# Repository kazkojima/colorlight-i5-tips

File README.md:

# Colorlight i5 Tips

This is a tiny collection of tips for [Colorlight i5 FPGA board](https://github.com/wuxx/Colorlight-FPGA-Projects).

## Quick start

See [Tom Verbeure's great article](https://tomverbeure.github.io/2021/01/22/The-Colorlight-i5-as-FPGA-development-board.html) first. It's a complete guide for the board and its environment ATM.

See also [get-start](https://github.com/wuxx/Colorlight-FPGA-Projects/blob/master/get-start.md) of the above original site. The board has the CMSIS-DAP link for debug and serial port. The site gives the "dapprog" which is a wrapper script of OpenOCD for convenience.

```
$ ./dapprog xxx.svf # Configure with xxx.svf
$ ./dapprog xxx.bit # Write configuration to the flash
```

though the 2nd one fails because the flash is protected in shipping. See SPIFLASH below. If you follows the Tom's article, this problem can be avoided with "ecpdap".

```
$ ecpdap flash unprotect
```

See 'Programming a Bitstream into SPI flash' section of his article for details.
For loading and flash writing,

```
$ ecpdap program xxx.bit       # Configure with xxx.svf
$ ecpdap flash erase           # Erase flash
$ ecpdap flash write xxx.bit   # Write configuration to the flash
```

## LiteX

Now [litex-board](https://github.com/litex-hub/litex-boards) has colorlight i5 board support. It uses [Adam Greig's ecpdap](https://github.com/adamgreig/ecpdap) as the bit stream loader written in Rust.

For LiteX, see [Quick start guide of LiteX](https://github.com/enjoy-digital/litex#quick-start-guide).

```
$ wget https://raw.githubusercontent.com/enjoy-digital/litex/master/litex_setup.py
$ chmod +x litex_setup.py
$ ./litex_setup.py init install --user
```

should prepare the LiteX tree.

After these steps,

```
$ cd litex-boards/litex_boards/targets
$ ./colorlight_i5.py --with-sdcard --integrated-rom-size 0xc000 --l2-size 2048
```

for example, will generate .v and .lpf files in litex-boards/litex_boards/targets/build/colorlight_i5/gateware directory.

```
$ cd build/colorlight_i5/gateware
$ /bin/sh ./build_colorlight_i5.sh
```

will build .svf and .bin stream files.

With --build option

```
$ ./colorlight_i5.py --with-sdcard --with-spi --integrated-rom-size 0xc000 --l2-size 2048 --build
```

build_colorlight_i5.sh runs automatically. If ecpdap is installed already, --load option programs FPGA with the stream built

```
$ ./colorlight_i5.py --with-sdcard --with-spi --integrated-rom-size 0xc000 --l2-size 2048 --load
```

## SPIFLASH

[The start guide](https://github.com/wuxx/Colorlight-FPGA-Projects/blob/master/get-start.md) says that the SPI-Flash on i5 modules GD25Q16, is locked. You can free the lock with ecpdap.

## SDCARD

I've tested DIGILENT MicroSD PMOD.

It seems that the pull-up is a bit weak to work with the higher clock. An added 1k pull-up register to MOSI/CMD line works for me.

## Ethernet

Colorlight i5 has two Braodcom's B50612D gigabit ethernet transceiver chips. I made a simple extender with pulse transformer and RJ45 connector to test ethernet. i5ether directory includes KiCad files for it.

netboot works with it.

B50612D datasheet says that the pin 41 of the chip PHYA[0] determines the PHY Address of B50612D. It seems that the chip connected to ETH2_* connecter pins has PHYA[0] = 0 and the LiteX ether MAC works with this PHY. ~~ATM, the platform file defines this chip as the 2nd ether so as to match the connector pins.~~ The order of the two PHYs is swapped with the naming of the connectors on the board so to match with the configuration of their PHYA[0] pins. The default is "--eth-phy 0".

~~The build option "--eth-phy 1" will make ETH2_* pins the working ethernet port.~~

```
$ ./colorlight_i5.py --integrated-rom-size 0xc000 --l2-size 2048 --with-sdcard --with-ethernet
```

## HDMI

The build option "--with-video-framebuffer" (resp. "--with-video-terminal") makes the experimental support for video frame buffer (resp. video terminal) enable. The configuration of the HDMI output pins on the Muse-lab development board are assumed.

--with-video-framebuffer and --with-video-terminal will consume some RAM blocks of ECP5. If these options are used with --with-ethernet, for example, the build may fail due to the shortage of BRAM(DP16KD). One could reduce the usage of BRAM with specifying the lower values of integrated-sram-size and l2-size. Here are some examples.

```
$ ./colorlight_i5.py --with-ethernet --with-video-framebuffer --integrated-rom-size 0xa000 --integrated-sram-size 0x1000 --l2-size 2048 --build --load

$ ./colorlight_i5.py --with-ethernet --with-video-terminal --integrated-rom-size 0xa000 --integrated-sram-size 0x1000 --l2-size 1024 --build --load
```

The video fame buffer has a data skew issue on colorlight i5 ATM. It can be avoided temporarily with the one liner below:

```
diff --git a/litex_boards/targets/colorlight_i5.py b/litex_boards/targets/colorlight_i5.py
index 58aacfc..f081f43 100755
--- a/litex_boards/targets/colorlight_i5.py
+++ b/litex_boards/targets/colorlight_i5.py
@@ -150,7 +150,7 @@ class BaseSoC(SoCCore):
                 size                    = kwargs.get("max_sdram_size", 0x40000000),
                 l2_cache_size           = kwargs.get("l2_size", 8192),
                 l2_cache_min_data_width = kwargs.get("min_l2_data_width", 128),
-                l2_cache_reverse        = True
+                l2_cache_reverse        = False if with_video_framebuffer else True
             )
 
         # Ethernet / Etherbone ---------------------------------------------------------------------
```

## Zephyr

Links:

[Minimal Zephyr OS on RISC-V and other tests](https://blog.pcbxprt.com/index.php/2020/07/26/minimal-zephyr-os-on-risc-v-and-other-tests/)

[his github repo](https://github.com/ghent360/riscvOnColorlight-5A-75B)

Install Zephyr and make a modification for colorlight as written in the blog.

Although it may not be necessary in your environment, on my Ubuntu 20.04 TLS system, I needed a complete python-3.7 environment for building zephyr itself and its examples. It can be done

```
$ conda create --name py37 python=3.7
$ conda activate py37
```

if you have installed Anaconda.

Zephyr's Litex-vexrisc support expects 8-bit CSRs as well as linux. OTOH LiteX produces a 32-bit CSR SoC by default, so that needs to be changed with --csr-data-width 8 option.

```
$ ./colorlight_i5.py --with-sdcard --with-ethernet --integrated-rom-size 0xc000 --l2-size 2048 --csr-data-width 8
```

Also 2 DT-related zephyr's files

```
dts/riscv/riscv32-litex-vexriscv.dtsi
boards/riscv/litex_vexriscv/litex_vexriscv.dts
```

need to be modified for the changes in the configuration of the SoC, frequencies and the address of the CSRs. colorlight_i5.py generates build/colorlight_i5/software/include/generated/csr.h which contains the CSR's address information when building SoC RTL.

The simple example like blinky works successfully, though it looks some litex drivers in zephyr are WIP and not full-featured.

#### Updates for Zephyr

I've pushed [zephyr-rtos branch with modified DTS and default configs for colorlight-i5](https://github.com/kazkojima/zephyr/tree/colorlight_i5).

You can try net samples with it.

```
$ cd zephyrproject/zephyr/samples/net/telnet
$ mkdir build
$ cd build
$ cmake -DBOARD=litex_vexriscv ..
$ make menuconfig # optional
$ make
```

makes zephyr/zephyr.bin binary which can be used as a litex boot.bin.

## linux-on-litex-vexriscv

In the following sections, linux-on-litex-vexriscv HEAD and litex-hub/linux litex-rebase branch HEAD are assumed.

Due to the 8MB memory limit, it's difficult to put the root filesystem on the RAM like other boards. Putting it on NFS or micro SD will be a good candidate. Linux can boot on these two settings, though it's very slow. The main reason would be that there is not enough physical memory to keep a sufficient working set.

Since we have only 8GB of memory, we need to change the memory map for the device table and emulator binaries. The patch in linux/ assumes rv32.dtb at 0x40780000 and opensbi.bin at 0x407c0000.
There is a boot.json file in linux/ that matches this change.

### sdcard root

To make the micro SD the root FS, I'm using the litex-rebase branch of [litex's linux tree](https://github.com/litex-hub/linux.git), [a tiny patch for mmc](https://github.com/kazkojima/colorlight-i5-tips/blob/main/linux/linux-litex-vexriscv-rebase-mmc.patch) and [.config for mmc](https://github.com/kazkojima/colorlight-i5-tips/blob/main/linux/defconfig-colorlight-i5-mmc) and [linux-on-litex-vexriscv](https://github.com/litex-hub/linux-on-litex-vexriscv).

linux-on-litex-vexriscv includes some kernel patches required for litex.

```
$ for f in YOUR_linux-on-litex-vexriscv_PATH/buildroot/patches/linux/000[124]*.patch; do (cat $f | patch -p1); done
```

in the linux source directory will add these patches, ATM. Without them, the resulted kernel size is over 20GB!!

Currently colorlight i5 sdcard support is experimental and isn't yet merged. [A tiny patch](https://github.com/kazkojima/colorlight-i5-tips/blob/main/linux/linux-on-litex-vexriscv-mmc.patch) is needed for linux-on-litex-vexriscv.

```
$ cd YOUR_linux-on-litex-vexriscv_PATH
$ cat linux-on-litex-vexriscv-mmc.patch | patch -p1
$ ./make.py --board colorlight_i5 --build
```

### Ethernet/nfsroot

Almost similar to sdcard root, except no mmc patch for kernel isn't required and [DT for ethernet/nfsroot](https://github.com/kazkojima/colorlight-i5-tips/blob/main/linux/rv32-eth.dts)  [.config for nfsroot](https://github.com/kazkojima/colorlight-i5-tips/blob/main/linux/defconfig-colorlight-i5-eth) have worked. 

~~### SDRAM issue on linux-on-litex-vexriscv HEAD~~

This is solved with [commit dee4331](https://github.com/litex-hub/linux-on-litex-vexriscv/commit/dee4331dc39124bca37f8f765ac20184ad447ae4)!

### OpenSBI

A tiny patch [opensbi-config-fixmap.patch](https://github.com/kazkojima/colorlight-i5-tips/blob/main/linux/opensbi-config-fixmap.patch) for OpenSBI is needed so as to match 8MB RAM.

```
$ clone https://github.com/litex-hub/opensbi --branch 0.8-linux-on-litex-vexriscv
$ cd opensbi
$ cat opensbi-config-fixmap.patch | patch -p1
$ make CROSS_COMPILE=riscv32-unknown-elf- PLATFORM=litex/vexriscv
$ cp build/platform/litex/vexriscv/firmware/fw_jump.bin opensbi.bin
```

will give opensbi.bin that works on the 8MB memory map.

## Litescope

TODO

## History

### Updates (Mar 26 2021)

* Add HDMI section.
* Remove the old spiflash stuff.

### Updates (Feb 16 2021)

* Fix ecpdap command to write flash.
* Add example command lines to build a zephyr sample.

### Updates (Jan 30 2021)

* Add an OpenSBI subsection.

### Updates (Jan 29 2021)

* Update for merging colorlight i5 board support.
* uSD-pmod pull-up register issue.

### Updates (Jan 27 2021)

* Adjust for linux-on-litex-vexriscv HEAD.
* Remove 'Reset switch' section.

### Updates (Jan 19 2021)

* Add about forked Zephyr OS with colorlight_i5 branch.

### Updates (Jan 15 2021)

* Fix initial builds.

### Updates (Jan 6 2021)

* Change the order of ethernet PHYs.
* Add a PHY configuration to BIOS.
* Add a linux patch and .dts so as to enable the interrupt on the ethernet.

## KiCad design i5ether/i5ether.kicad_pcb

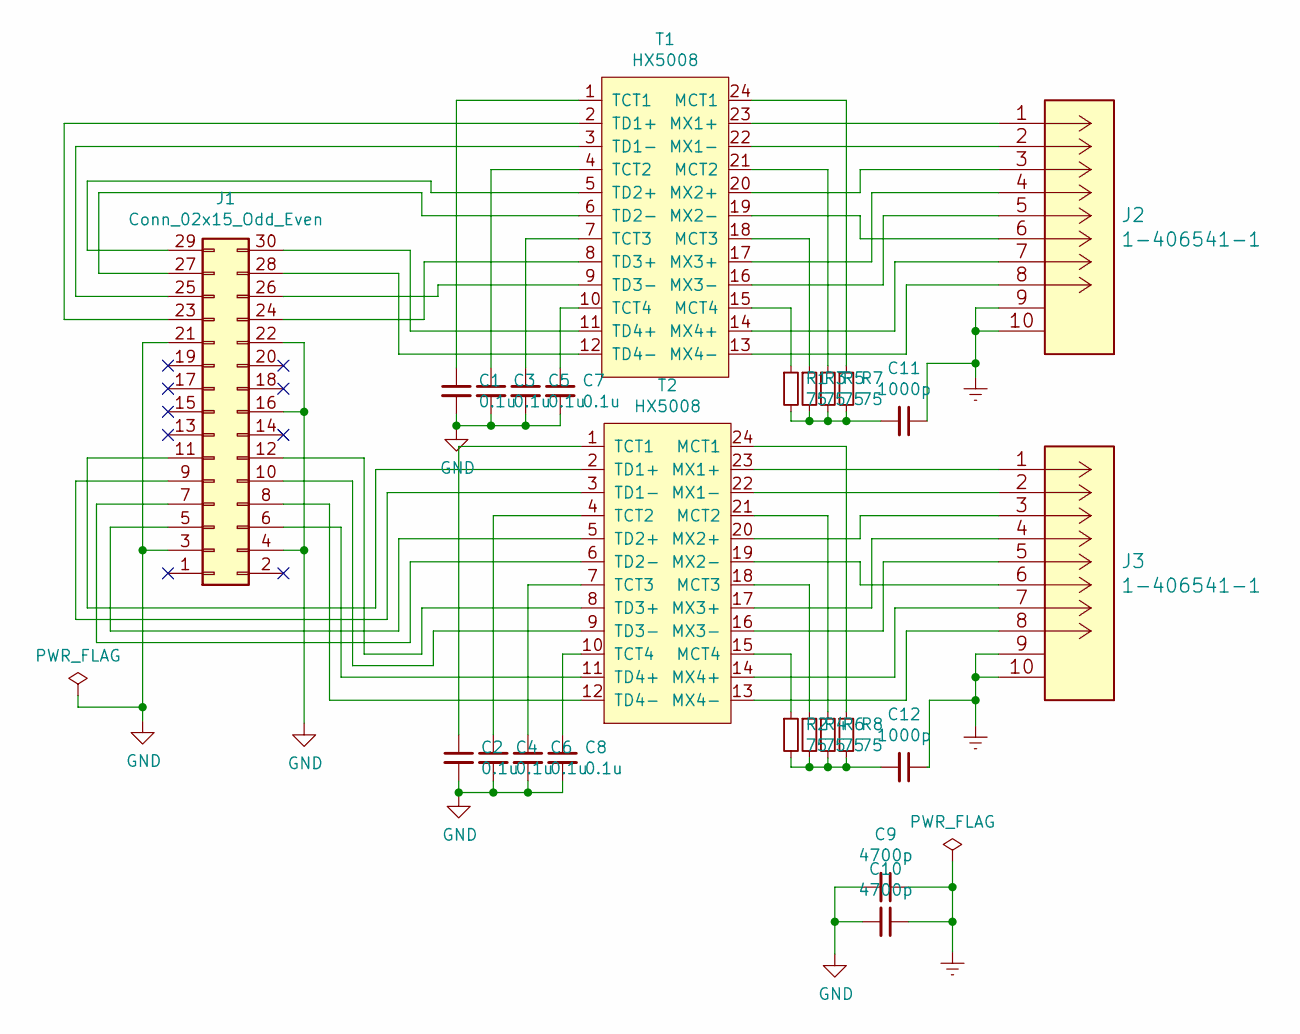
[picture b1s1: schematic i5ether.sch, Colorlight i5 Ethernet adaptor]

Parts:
C1, C2, C3, C4, C5, C6, C7, C8: 0.1u; C_0402_1005Metric
C9, C10: 4700p; R_1812_4532Metric
C11, C12: 1000p; C_0402_1005Metric
J1: Conn_02x15_Odd_Even; PinHeader_2x15_P2.54mm_Horizontal
J2, J3: 1-406541-1
R1, R2, R3, R4, R5, R6, R7, R8: 75; R_0402_1005Metric
T1, T2: HX5008; HX5008NL

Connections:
Earth: C9.1, C10.1, C11.1, C12.1, J2.9 (SHIELD), J2.10 (SHIELD), J3.9 (SHIELD), J3.10 (SHIELD)
GND: C1.2, C2.2, C3.2, C4.2, C5.2, C6.2, C7.2, C8.2, C9.2, C10.2, J1.3, J1.4, J1.16, J1.21, J1.22
unnamed: C1.1, T1.1 (TCT1)
unnamed: C2.1, T2.1 (TCT1)
unnamed: C3.1, T1.4 (TCT2)
unnamed: C4.1, T2.4 (TCT2)
unnamed: C5.1, T1.7 (TCT3)
unnamed: C6.1, T2.7 (TCT3)
unnamed: C7.1, T1.10 (TCT4)
unnamed: C8.1, T2.10 (TCT4)
unnamed: C11.2, R1.2, R3.2, R5.2, R7.2
unnamed: C12.2, R2.2, R4.2, R6.2, R8.2
unnamed: J1.5, T2.5 (TD2+)
unnamed: J1.6, T2.11 (TD4+)
unnamed: J1.7, T2.6 (TD2-)
unnamed: J1.8, T2.12 (TD4-)
unnamed: J1.9, T2.3 (TD1-)
unnamed: J1.10, T2.9 (TD3-)
unnamed: J1.11, T2.2 (TD1+)
unnamed: J1.12, T2.8 (TD3+)
unnamed: J1.23, T1.2 (TD1+)
unnamed: J1.24, T1.8 (TD3+)
unnamed: J1.25, T1.3 (TD1-)
unnamed: J1.26, T1.9 (TD3-)
unnamed: J1.27, T1.6 (TD2-)
unnamed: J1.28, T1.12 (TD4-)
unnamed: J1.29, T1.5 (TD2+)
unnamed: J1.30, T1.11 (TD4+)
unnamed: J2.1, T1.23 (MX1+)
unnamed: J2.2, T1.22 (MX1-)
unnamed: J2.3, T1.20 (MX2+)
unnamed: J2.4, T1.17 (MX3+)
unnamed: J2.5, T1.16 (MX3-)
unnamed: J2.6, T1.19 (MX2-)
unnamed: J2.7, T1.14 (MX4+)
unnamed: J2.8, T1.13 (MX4-)
unnamed: J3.1, T2.23 (MX1+)
unnamed: J3.2, T2.22 (MX1-)
unnamed: J3.3, T2.20 (MX2+)
unnamed: J3.4, T2.17 (MX3+)
unnamed: J3.5, T2.16 (MX3-)
unnamed: J3.6, T2.19 (MX2-)
unnamed: J3.7, T2.14 (MX4+)
unnamed: J3.8, T2.13 (MX4-)
unnamed: R1.1, T1.15 (MCT4)
unnamed: R2.1, T2.15 (MCT4)
unnamed: R3.1, T1.18 (MCT3)
unnamed: R4.1, T2.18 (MCT3)
unnamed: R5.1, T1.21 (MCT2)
unnamed: R6.1, T2.21 (MCT2)
unnamed: R7.1, T1.24 (MCT1)
unnamed: R8.1, T2.24 (MCT1)

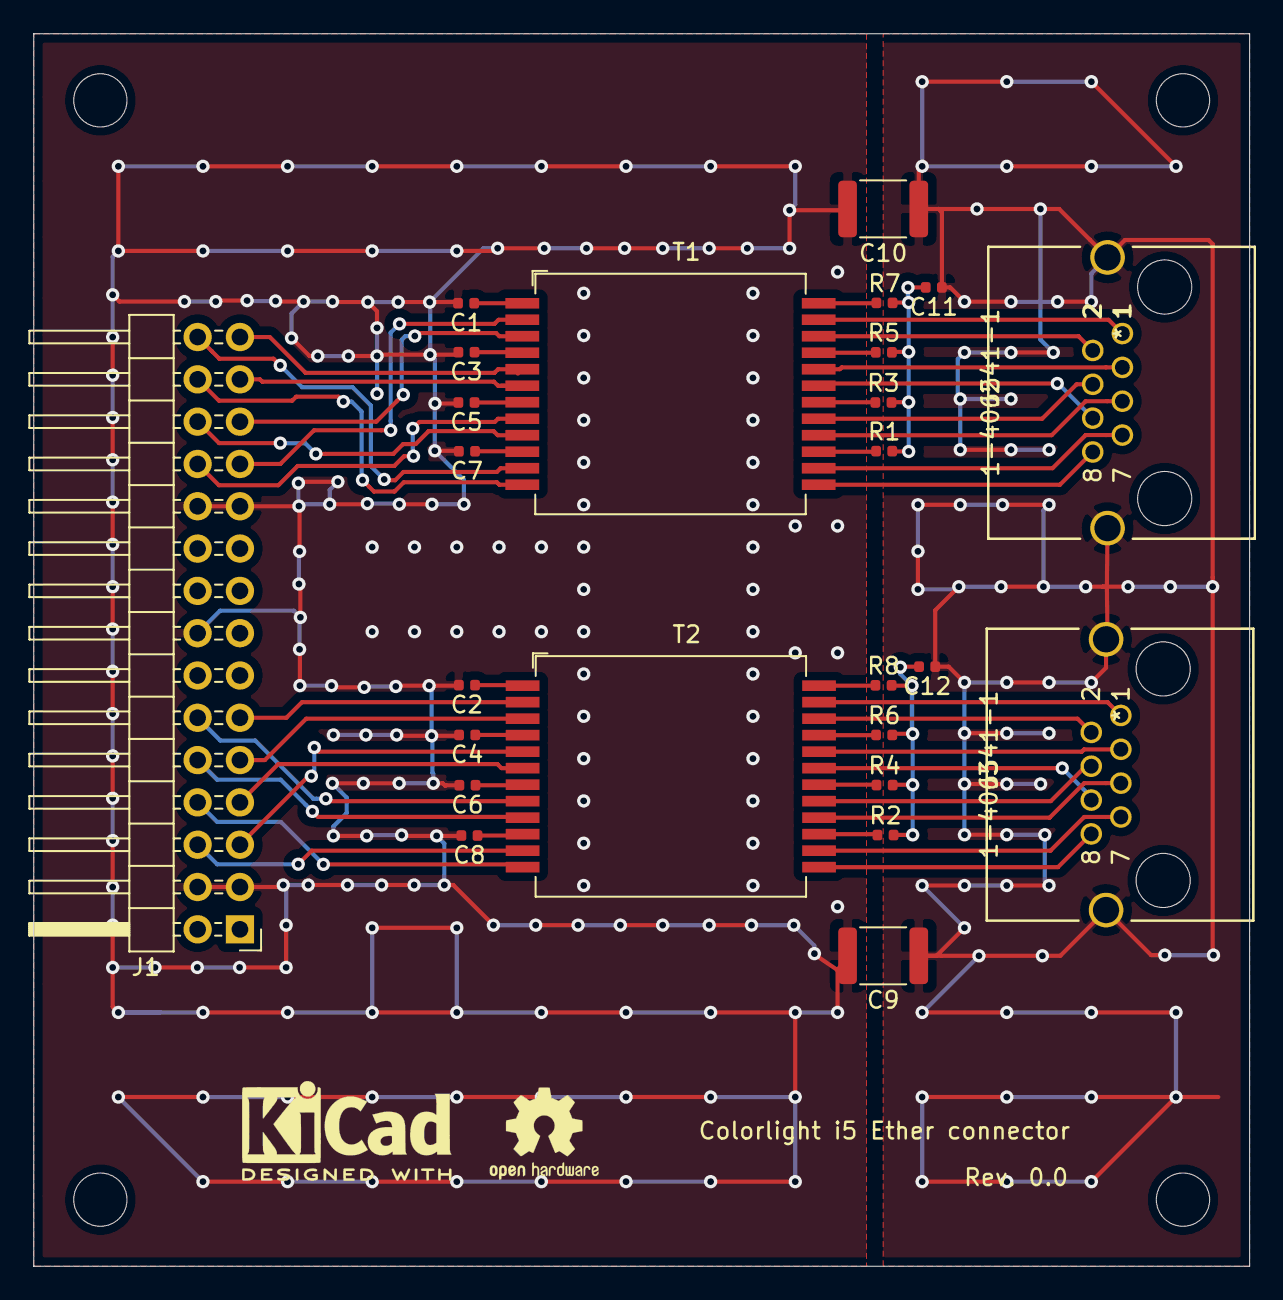
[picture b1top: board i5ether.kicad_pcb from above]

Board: 2 copper layers, 73.0 x 74.0 mm, 25 parts (0 on the bottom side), 52 nets.

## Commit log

2020-12-07 Initial commit.
2020-12-07 README.md: Fix image links.
2020-12-08 README.md: Update.
2020-12-11 README.md: Use cpu_reset_n instead of main_reset.
2020-12-13 README.md: Fix typos.
2020-12-20 Update for ether.
2020-12-23 README.md: Fix typo.
2021-01-05 Update linux/linux-on-litex-vexriscv-colorlight-i5.patch.
2021-01-06 Update README.md.
2021-01-06 Update linux patches.
2021-01-06 Add a verilog patch.
2021-01-15 Update.
2021-01-19 Update for zephyr.
2021-01-19 RAEDME.md: Correct duplicate parts.
2021-01-19 RAEDME.md: Correct parentheses.
2021-01-19 README: Fix a wrong link.
2021-01-23 README.md: Add a reference to Tom Verbeure's great article.
2021-01-27 RAEDME.md: Update.
2021-01-29 README.md: Update for merging colorlight i5 board support.
2021-01-30 Add a patch for OpenSBI.
2021-02-16 README.md: Update zephyr section.
2021-02-16 README.md: Fix&add ecpdap command lines.
2021-03-26 Add HDMI section.

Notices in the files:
parts and their libraries:
Copyright 2016 Accelerated Designs. All rights reserved.
